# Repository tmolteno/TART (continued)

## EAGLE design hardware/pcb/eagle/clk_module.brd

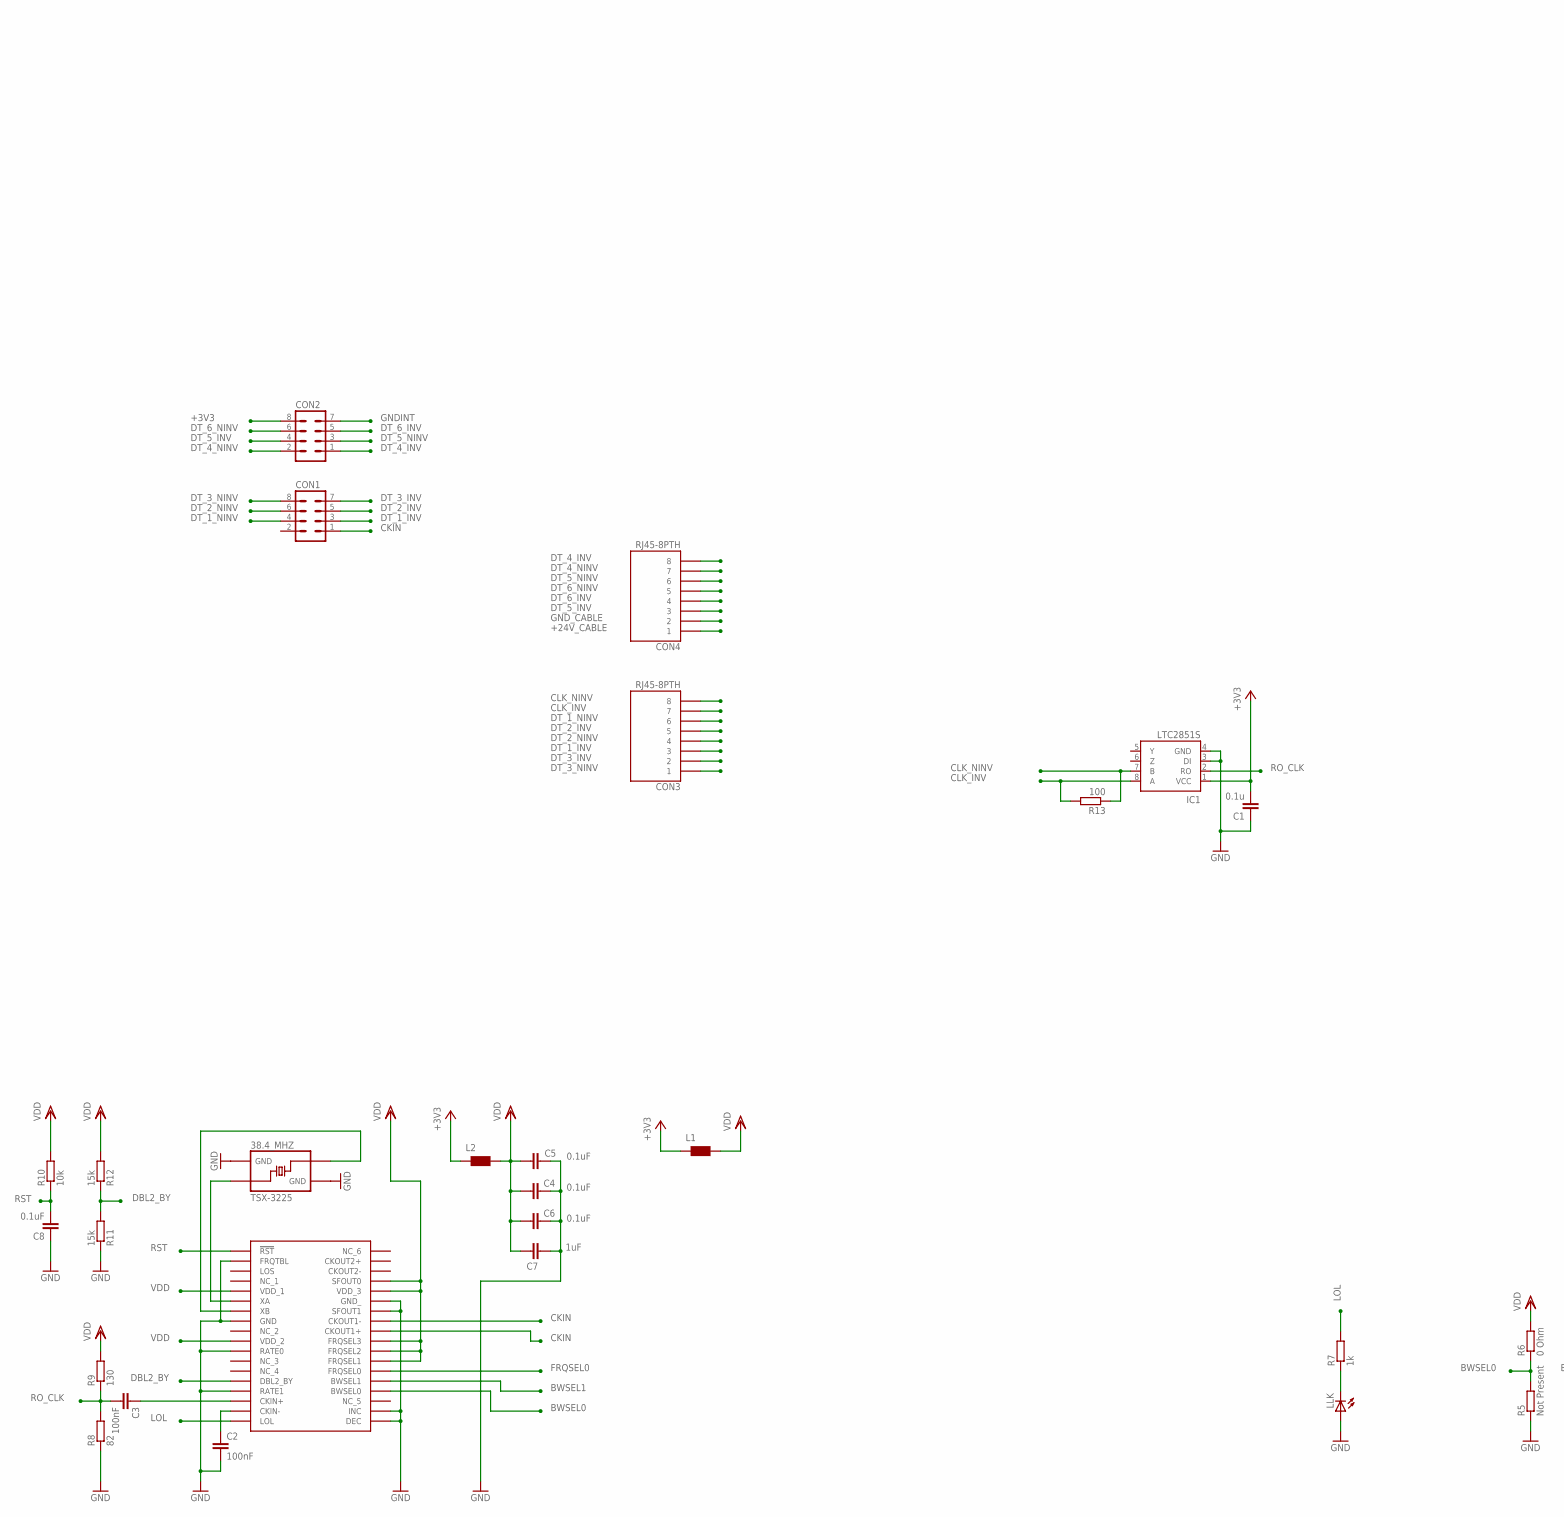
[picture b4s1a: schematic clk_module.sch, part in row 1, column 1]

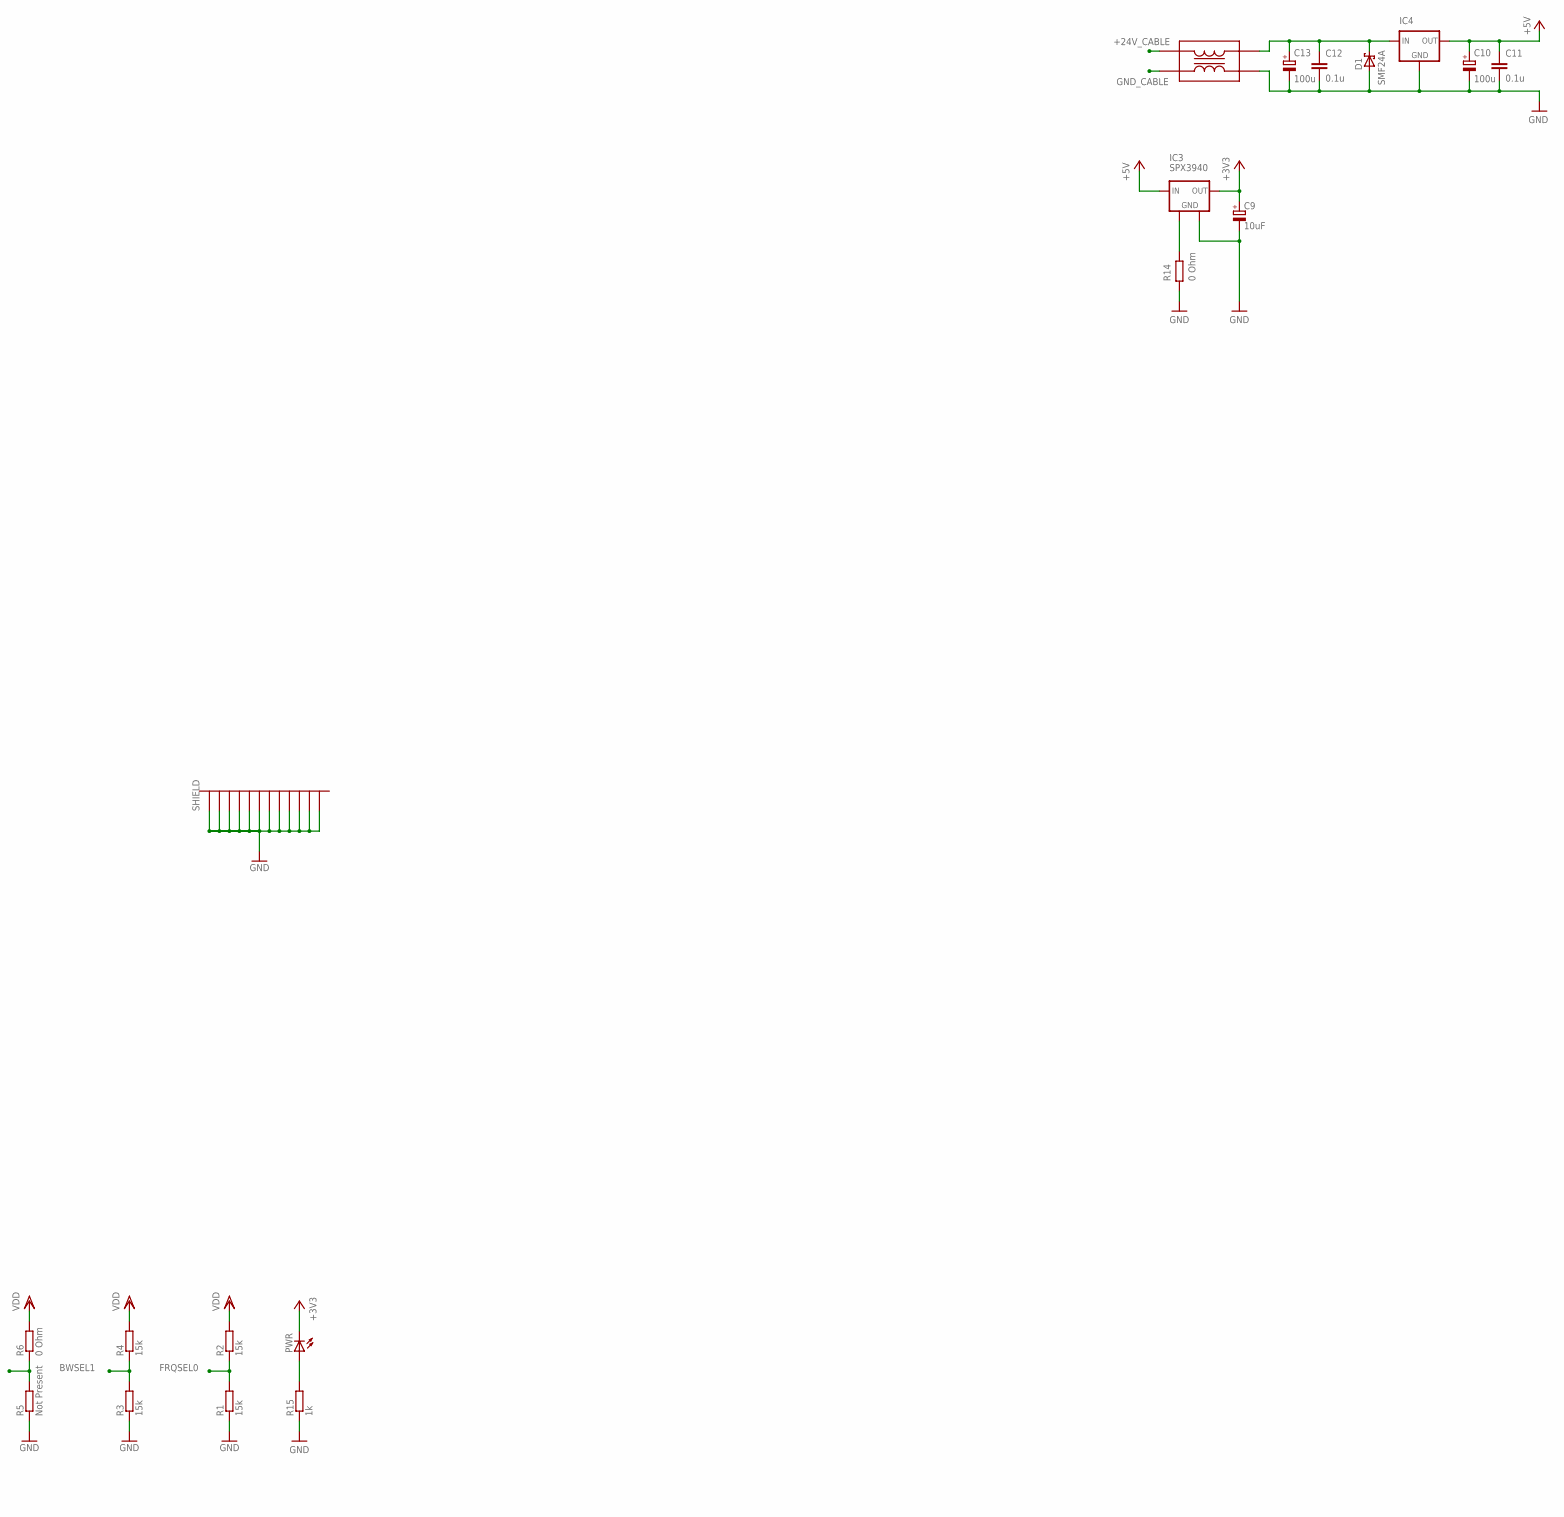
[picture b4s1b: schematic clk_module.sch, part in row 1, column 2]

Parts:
38.4_MHZ: TSX-3225
C1, C11, C12: 0.1u; C0805
C2, C3: 100nF; C0402
C4, C5, C6, C8: 0.1uF; C0402
C7: 1uF; C0402
C9: 10uF; E2-5
C10, C13: 100u; E5-10,5
CON1, CON2: MA04-2
CON3, CON4: RJ45-8PTH; RJ45-8
D1: SMF24A; SOD123
IC1: LTC2851S; SOIC8
IC2: SI5317; QFN-36
IC3: SPX3940; SOT223
IC4: V_REG_OKI-78SRSINK; TO220-IGO
L1, L2: WE-CBF_0805; 0805
L3: ACM3225-601-2P-T001
LLK: LEDCHIPLED_0805; CHIPLED_0805
PWR: LEDCHIPLED_0805; CHIPLED_0805
R1, R2, R3, R4, R11, R12: 15k; R0603
R5: Not Present; R0603
R6: 0 Ohm; R0603
R7, R15: 1k; R0603
R8: 82; R0603
R9: 130; R0603
R10: 10k; R0402
R13: 100; R0603
R14: 0 Ohm; R0805
SH1: BMIS-202

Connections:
24V_IN: C12.1, C13.+, D1.C, IC4.IN, L3.4
+3V3: C1.2, C9.+, CON2.8, IC1.1 (VCC), IC3.3 (OUT), L1.1, L2.1, PWR.C
+5V: C10.+, C11.1, IC3.1 (IN), IC4.OUT
+24V_CABLE: CON4.1, L3.1
BWSEL0: IC2.22 (BWSEL0), R5.2, R6.1
BWSEL1: IC2.23 (BWSEL1), R3.2, R4.1
CKIN: CON1.1, IC2.28 (CKOUT1+), IC2.29 (CKOUT1-)
CKIN+: C3.1, IC2.16 (CKIN+)
CKIN-: C2.1, IC2.17 (CKIN-)
CLK_INV: CON3.7, IC1.8 (A), R13.2
CLK_NINV: CON3.8, IC1.7 (B), R13.1
DBL2_BY: IC2.14 (DBL2_BY), R11.2, R12.1
DT_1_INV: CON1.3, CON3.3
DT_1_NINV: CON1.4, CON3.6
DT_2_INV: CON1.5, CON3.5
DT_2_NINV: CON1.6, CON3.4
DT_3_INV: CON1.7, CON3.2
DT_3_NINV: CON1.8, CON3.1
DT_4_INV: CON2.1, CON4.8
DT_4_NINV: CON2.2, CON4.7
DT_5_INV: CON2.4, CON4.3
DT_5_NINV: CON2.3, CON4.6
DT_6_INV: CON2.5, CON4.4
DT_6_NINV: CON2.6, CON4.5
FRQSEL0: IC2.24 (FRQSEL0), R1.2, R2.1
GND: 38.4_MHZ.PIN_2 (GND_2), 38.4_MHZ.PIN_4 (GND_1), C1.1, C2.2, C4.1, C5.1, C6.1, C7.1, C8.1, IC1.3 (DI), IC1.4 (GND), IC2.2 (FRQTBL), IC2.8 (GND), IC2.11 (RATE0), IC2.15 (RATE1), IC2.19 (DEC), IC2.20 (INC), IC2.30 (SFOUT1), IC2.31 (GND_), IC2.GND_PAD (GND), IC2.GND_VIA_1 (GND), IC2.GND_VIA_2 (GND), IC2.GND_VIA_3 (GND), IC2.GND_VIA_4 (GND), IC2.GND_VIA_5 (GND), LLK.A, R1.1, R3.1, R5.1, R8.1, R11.1, R14.1, SH1.P$1, SH1.P$2, SH1.P$3, SH1.P$4, SH1.P$5, SH1.P$6, SH1.P$7, SH1.P$8, SH1.P$9, SH1.P$10, SH1.P$11, SH1.P$12
GNDINT: C9.-, C10.-, C11.2, C12.2, C13.-, CON2.7, D1.A, IC3.2 (GND), IC3.4 (GND), IC4.GND, L3.3, R14.2, R15.1
GND_CABLE: CON4.2, L3.2
LOL: IC2.18 (LOL), R7.2
unnamed: PWR.A, R15.2
unnamed: LLK.C, R7.1
RO_CLK: C3.2, IC1.2 (RO), R8.2, R9.1
RST: C8.2, IC2.1 (!RST), R10.1
VDD: C4.2, C5.2, C6.2, C7.2, IC2.5 (VDD_1), IC2.10 (VDD_2), IC2.25 (FRQSEL1), IC2.26 (FRQSEL2), IC2.27 (FRQSEL3), IC2.32 (VDD_3), IC2.33 (SFOUT0), L2.2, R10.2, R12.2
VDD_2: L1.2, R2.2, R4.2, R6.2, R9.2
XA: 38.4_MHZ.PIN_1 (CON_1), IC2.6 (XA)
XB: 38.4_MHZ.PIN_3 (CON_2), IC2.7 (XB)

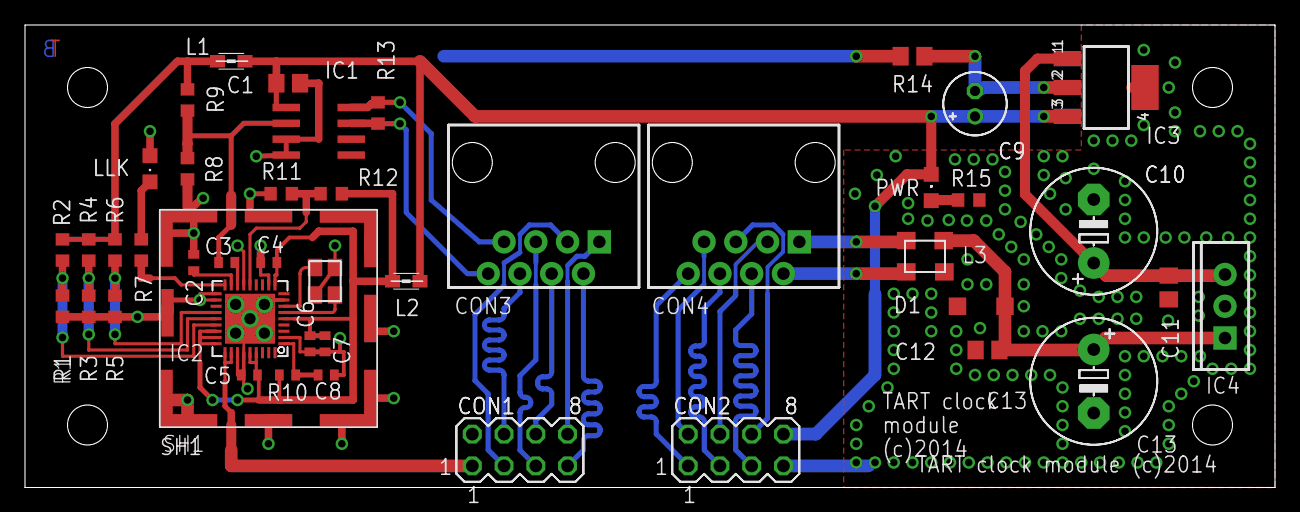
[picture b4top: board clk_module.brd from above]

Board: 2 copper layers, 100.0 x 37.0 mm, 44 parts (0 on the bottom side), 37 nets.

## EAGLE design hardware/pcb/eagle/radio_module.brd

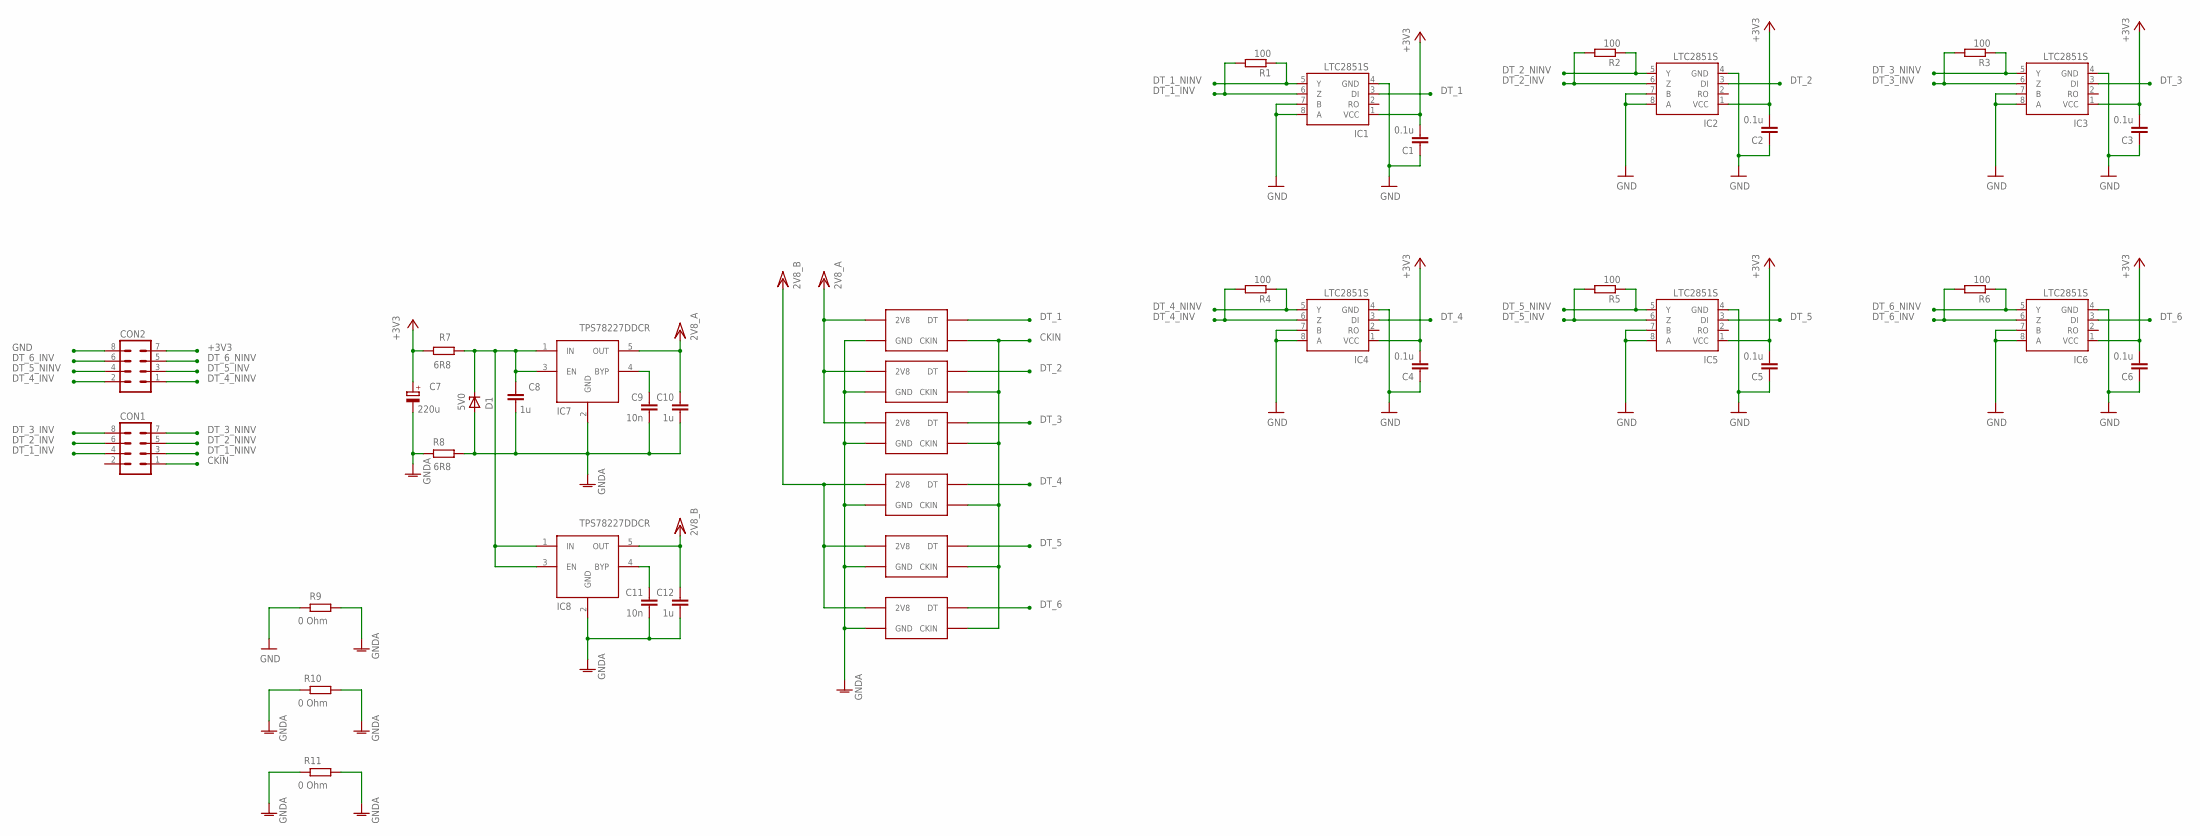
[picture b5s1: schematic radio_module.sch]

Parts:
C1, C2, C3, C4, C5, C6: 0.1u; C0805
C7: 220u; C1210
C8, C10, C12: 1u; C0603
C9, C11: 10n; C0603
CON1, CON2: MA04-2
D1: 5V0; SOD523
IC1, IC2, IC3, IC4, IC5, IC6: LTC2851S; SOIC8
IC7, IC8: TPS78227DDCR; SOT23-5
MOD_1, MOD_2, MOD_3, MOD_4, MOD_5, MOD_6: GPS_RADIO_MODULE
R1, R2, R3, R4, R5, R6: 100; R0603
R7: 6R8; R0805
R8: 6R8; R0603
R9, R10, R11: 0 Ohm; R0805

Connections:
+2V8_A: C10.1, IC7.5 (OUT), MOD_1.2V8@11 (2V8), MOD_1.2V8@15 (2V8), MOD_1.2V8@16 (2V8), MOD_2.2V8@11 (2V8), MOD_2.2V8@15 (2V8), MOD_2.2V8@16 (2V8), MOD_3.2V8@11 (2V8), MOD_3.2V8@15 (2V8), MOD_3.2V8@16 (2V8)
+2V8_B: C12.1, IC8.5 (OUT), MOD_4.2V8@11 (2V8), MOD_4.2V8@15 (2V8), MOD_4.2V8@16 (2V8), MOD_5.2V8@11 (2V8), MOD_5.2V8@15 (2V8), MOD_5.2V8@16 (2V8), MOD_6.2V8@11 (2V8), MOD_6.2V8@15 (2V8), MOD_6.2V8@16 (2V8)
+3V3: C1.2, C2.2, C3.2, C4.2, C5.2, C6.2, C7.1 (+), CON2.7, IC1.1 (VCC), IC2.1 (VCC), IC3.1 (VCC), IC4.1 (VCC), IC5.1 (VCC), IC6.1 (VCC), R7.2
BYP: C9.1, IC7.4 (BYP)
BYP1: C11.1, IC8.4 (BYP)
CKIN: CON1.1, MOD_1.CKIN@13 (CKIN), MOD_2.CKIN@13 (CKIN), MOD_3.CKIN@13 (CKIN), MOD_4.CKIN@13 (CKIN), MOD_5.CKIN@13 (CKIN), MOD_6.CKIN@13 (CKIN)
DT_1: IC1.3 (DI), MOD_1.DT@12 (DT)
DT_1_INV: CON1.4, IC1.6 (Z), R1.2
DT_1_NINV: CON1.3, IC1.5 (Y), R1.1
DT_2: IC2.3 (DI), MOD_2.DT@12 (DT)
DT_2_INV: CON1.6, IC2.6 (Z), R2.2
DT_2_NINV: CON1.5, IC2.5 (Y), R2.1
DT_3: IC3.3 (DI), MOD_3.DT@12 (DT)
DT_3_INV: CON1.8, IC3.6 (Z), R3.2
DT_3_NINV: CON1.7, IC3.5 (Y), R3.1
DT_4: IC4.3 (DI), MOD_6.DT@12 (DT)
DT_4_INV: CON2.2, IC4.6 (Z), R4.2
DT_4_NINV: CON2.1, IC4.5 (Y), R4.1
DT_5: IC5.3 (DI), MOD_5.DT@12 (DT)
DT_5_INV: CON2.3, IC5.6 (Z), R5.2
DT_5_NINV: CON2.4, IC5.5 (Y), R5.1
DT_6: IC6.3 (DI), MOD_4.DT@12 (DT)
DT_6_INV: CON2.6, IC6.6 (Z), R6.2
DT_6_NINV: CON2.5, IC6.5 (Y), R6.1
GND: C1.1, C2.1, C3.1, C4.1, C5.1, C6.1, CON2.8, IC1.4 (GND), IC1.7 (B), IC1.8 (A), IC2.4 (GND), IC2.7 (B), IC2.8 (A), IC3.4 (GND), IC3.7 (B), IC3.8 (A), IC4.4 (GND), IC4.7 (B), IC4.8 (A), IC5.4 (GND), IC5.7 (B), IC5.8 (A), IC6.4 (GND), IC6.7 (B), IC6.8 (A), R9.2
GNDA: C7.2 (-), C8.2, C9.2, C10.2, C11.2, C12.2, D1.A, IC7.2 (GND), IC8.2 (GND), MOD_1.GND@1 (GND), MOD_1.GND@2 (GND), MOD_1.GND@3 (GND), MOD_1.GND@4 (GND), MOD_1.GND@5 (GND), MOD_1.GND@6 (GND), MOD_1.GND@7 (GND), MOD_1.GND@8 (GND), MOD_1.GND@9 (GND), MOD_1.GND@10 (GND), MOD_1.GND@14 (GND), MOD_1.V1 (GND), MOD_1.V2 (GND), MOD_1.V3 (GND), MOD_1.V4 (GND), MOD_1.V5 (GND), MOD_1.V6 (GND), MOD_1.V7 (GND), MOD_1.V8 (GND), MOD_1.V9 (GND), MOD_1.V10 (GND), MOD_1.V11 (GND), MOD_1.V12 (GND), MOD_1.V13 (GND), MOD_1.V14 (GND), MOD_1.V15 (GND), MOD_1.V16 (GND), MOD_1.V17 (GND), MOD_1.V18 (GND), MOD_1.V19 (GND), MOD_1.V20 (GND), MOD_1.V21 (GND), MOD_1.V22 (GND), MOD_1.V23 (GND), MOD_1.V24 (GND), MOD_1.V25 (GND), MOD_1.V26 (GND), MOD_1.V27 (GND), MOD_1.V28 (GND), MOD_1.V29 (GND), MOD_1.V30 (GND), MOD_2.GND@1 (GND), MOD_2.GND@2 (GND), MOD_2.GND@3 (GND), MOD_2.GND@4 (GND), MOD_2.GND@5 (GND), MOD_2.GND@6 (GND), MOD_2.GND@7 (GND), MOD_2.GND@8 (GND), MOD_2.GND@9 (GND), MOD_2.GND@10 (GND), MOD_2.GND@14 (GND), MOD_2.V1 (GND), MOD_2.V2 (GND), MOD_2.V3 (GND), MOD_2.V4 (GND), MOD_2.V5 (GND), MOD_2.V6 (GND), MOD_2.V7 (GND), MOD_2.V8 (GND), MOD_2.V9 (GND), MOD_2.V10 (GND), MOD_2.V11 (GND), MOD_2.V12 (GND), MOD_2.V13 (GND), MOD_2.V14 (GND), MOD_2.V15 (GND), MOD_2.V16 (GND), MOD_2.V17 (GND), MOD_2.V18 (GND), MOD_2.V19 (GND), MOD_2.V20 (GND), MOD_2.V21 (GND), MOD_2.V22 (GND), MOD_2.V23 (GND), MOD_2.V24 (GND), MOD_2.V25 (GND), MOD_2.V26 (GND), MOD_2.V27 (GND), MOD_2.V28 (GND), MOD_2.V29 (GND), MOD_2.V30 (GND), MOD_3.GND@1 (GND), MOD_3.GND@2 (GND), MOD_3.GND@3 (GND), MOD_3.GND@4 (GND), MOD_3.GND@5 (GND), MOD_3.GND@6 (GND), MOD_3.GND@7 (GND), MOD_3.GND@8 (GND), MOD_3.GND@9 (GND), MOD_3.GND@10 (GND), MOD_3.GND@14 (GND), MOD_3.V1 (GND), MOD_3.V2 (GND), MOD_3.V3 (GND), MOD_3.V4 (GND), MOD_3.V5 (GND), MOD_3.V6 (GND), MOD_3.V7 (GND), MOD_3.V8 (GND), MOD_3.V9 (GND), MOD_3.V10 (GND)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
unnamed: C8.1, D1.C, IC7.1 (IN), IC7.3 (EN), IC8.1 (IN), IC8.3 (EN), R7.1

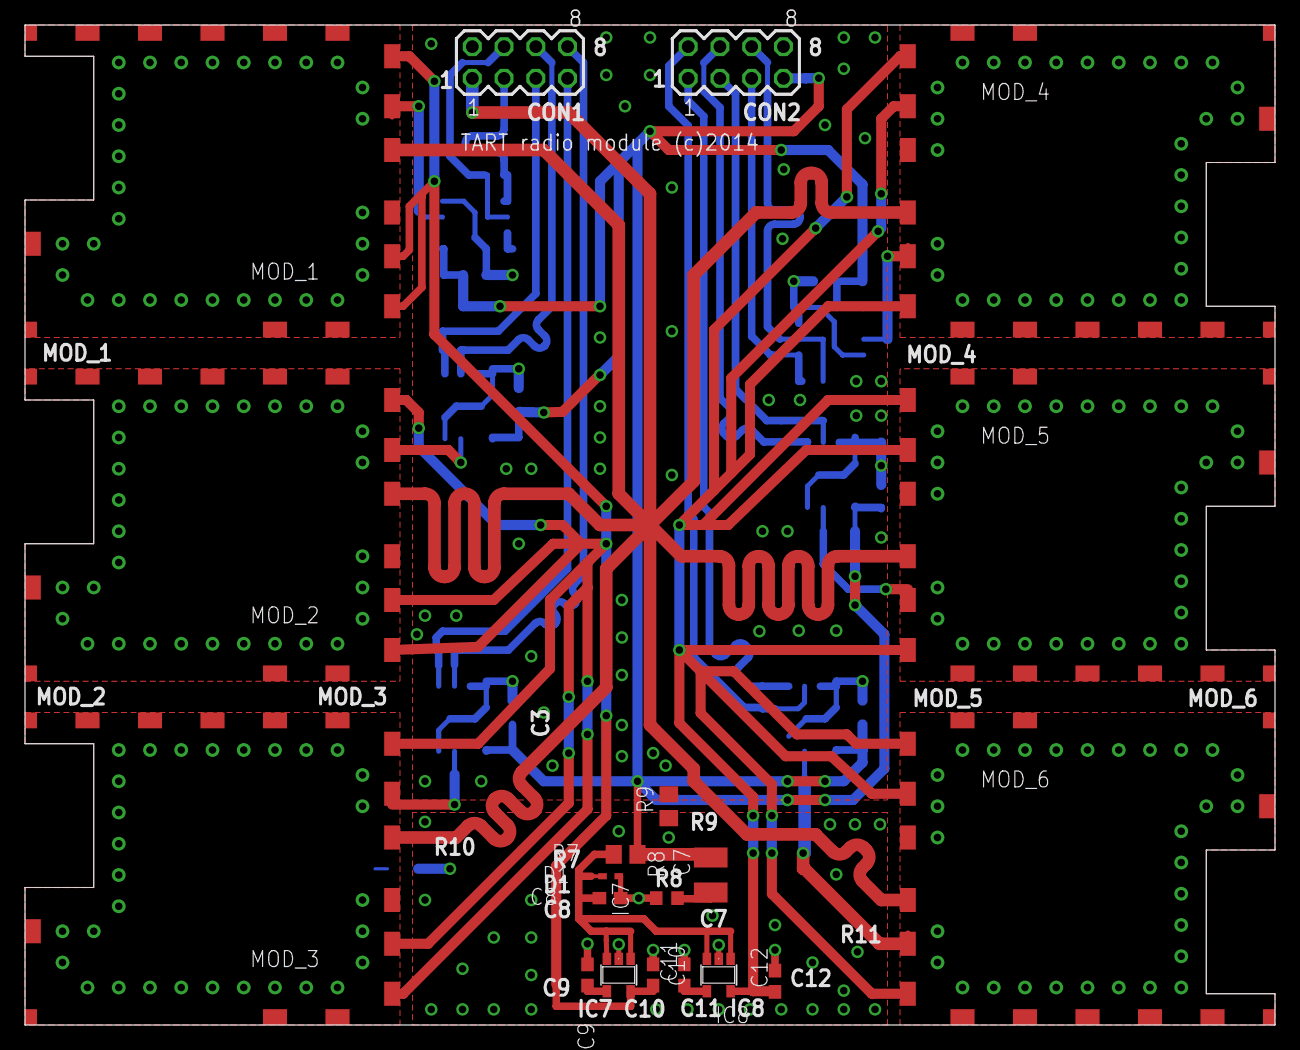
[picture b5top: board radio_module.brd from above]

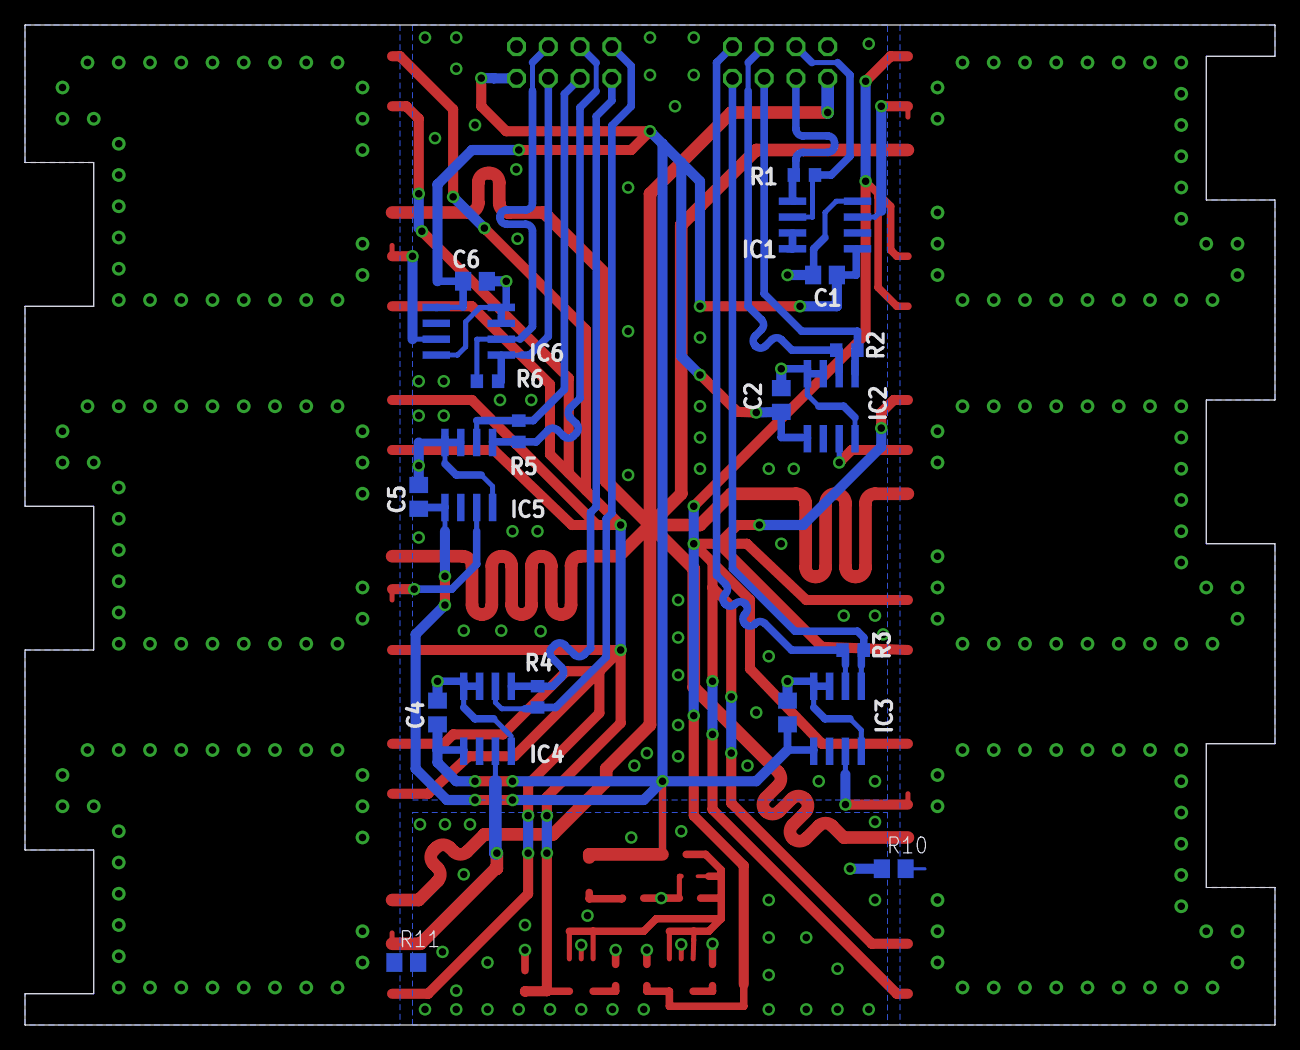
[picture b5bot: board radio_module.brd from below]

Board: 2 copper layers, 100.0 x 80.0 mm, 40 parts (20 on the bottom side), 27 nets.

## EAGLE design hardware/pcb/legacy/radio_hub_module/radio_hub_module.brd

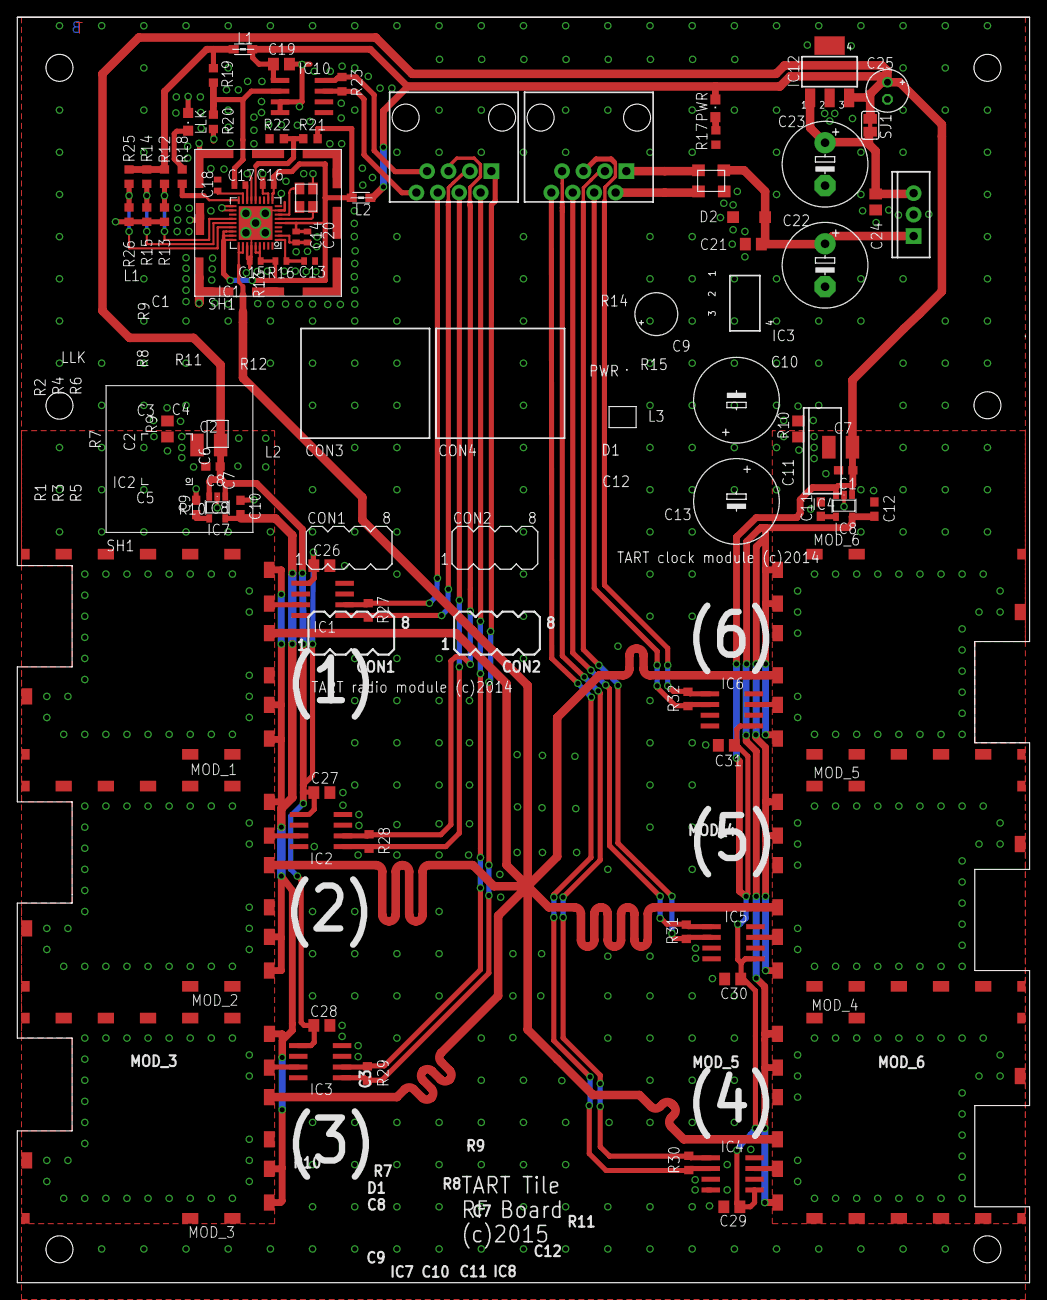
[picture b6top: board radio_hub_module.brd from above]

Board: 4 copper layers, 120.0 x 150.0 mm, 78 parts (0 on the bottom side), 48 nets.

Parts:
38.4_MHZ: TSX-3225
C1, C8, C10, C12: 1u; C0603
C2, C7: 220u; C1210
C9, C11: 10n; C0603
C13, C14, C15, C16: 0.1uF; C0402
C17, C18: 100nF; C0402
C19, C21, C24, C26, C27, C28, C29, C30, C31: 0.1u; C0805
C20: 1uF; C0402
C22, C23: 100u; E5-10,5
C25: 10uF; E2-5
CON3, CON4: RJ45-8PTH; RJ45-8
D2: SMF24A; SOD123
IC1, IC2, IC3, IC4, IC5, IC6, IC10: LTC2851S; SOIC8
IC7, IC8: TPS78227DDCR; SOT23-5
IC9: SI5317; QFN-36
IC11: OKI78s05; TO220-IGO
IC12: SPX3940; SOT223
L1, L2: 220w; 0805
L3: ACM3225-601-2P-T001
LLK: Grn; CHIPLED_0805
MOD_1, MOD_2, MOD_3, MOD_4, MOD_5, MOD_6: GPS_RADIO_MODULE
PWR: Red; CHIPLED_0805
R9, R10: 0 Ohm; R0805
R12: 0 Ohm; R0603
R13: Not Present; R0603
R14, R15, R21, R22, R25, R26: 15k; R0603
R16: 10k; R0402
R17, R18: 1k; R0603
R19: 130; R0603
R20: 82; R0603
R23, R27, R28, R29, R30, R31, R32: 100; R0603
SH1: BMIS-202
SJ1: SJ

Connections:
24V_IN: C21.1, C22.+, D2.C, IC11.IN, L3.4
!DT1: CON3.6, IC1.6, R27.2
!DT2: CON3.5, IC2.6, R28.2
!DT3: CON3.2, IC3.6, R29.2
!DT4: CON4.8, IC4.6, R30.2
!DT5: CON4.3, IC5.6, R31.2
!DT6: CON4.4, IC6.6, R32.2
!RST: C13.2, IC9.1, R16.1
+2V8_A: C10.1, IC7.5, MOD_1.2V8@11, MOD_1.2V8@15, MOD_1.2V8@16, MOD_2.2V8@11, MOD_2.2V8@15, MOD_2.2V8@16, MOD_3.2V8@11, MOD_3.2V8@15, MOD_3.2V8@16
+2V8_B: C12.1, IC8.5, MOD_4.2V8@11, MOD_4.2V8@15, MOD_4.2V8@16, MOD_5.2V8@11, MOD_5.2V8@15, MOD_5.2V8@16, MOD_6.2V8@11, MOD_6.2V8@15, MOD_6.2V8@16
+3V3: C1.1, C2.1, C7.1, C8.1, C19.2, C25.+, C26.2, C27.2, C28.2, C29.2, C30.2, C31.2, IC1.1, IC2.1, IC3.1, IC4.1, IC5.1, IC6.1, IC7.1, IC7.3, IC8.1, IC8.3, IC10.1, IC12.3, L1.1, L2.1, PWR.C, SJ1.2
+5V: C23.+, C24.1, IC11.OUT, IC12.1, SJ1.1
+24V_CABLE: CON4.1, L3.1
AGND: C2.2, C8.2, C9.2, C10.2, IC7.2, MOD_1.GND@1, MOD_1.GND@2, MOD_1.GND@3, MOD_1.GND@4, MOD_1.GND@5, MOD_1.GND@6, MOD_1.GND@7, MOD_1.GND@8, MOD_1.GND@9, MOD_1.GND@10, MOD_1.GND@14, MOD_1.V1, MOD_1.V2, MOD_1.V3, MOD_1.V4, MOD_1.V5, MOD_1.V6, MOD_1.V7, MOD_1.V8, MOD_1.V9, MOD_1.V10, MOD_1.V11, MOD_1.V12, MOD_1.V13, MOD_1.V14, MOD_1.V15, MOD_1.V16, MOD_1.V17, MOD_1.V18, MOD_1.V19, MOD_1.V20, MOD_1.V21, MOD_1.V22, MOD_1.V23, MOD_1.V24, MOD_1.V25, MOD_1.V26, MOD_1.V27, MOD_1.V28, MOD_1.V29, MOD_1.V30, MOD_2.GND@1, MOD_2.GND@2, MOD_2.GND@3, MOD_2.GND@4, MOD_2.GND@5, MOD_2.GND@6, MOD_2.GND@7, MOD_2.GND@8, MOD_2.GND@9, MOD_2.GND@10, MOD_2.GND@14, MOD_2.V1, MOD_2.V2, MOD_2.V3, MOD_2.V4, MOD_2.V5, MOD_2.V6, MOD_2.V7, MOD_2.V8, MOD_2.V9, MOD_2.V10, MOD_2.V11, MOD_2.V12, MOD_2.V13, MOD_2.V14, MOD_2.V15, MOD_2.V16, MOD_2.V17, MOD_2.V18, MOD_2.V19, MOD_2.V20, MOD_2.V21, MOD_2.V22, MOD_2.V23, MOD_2.V24, MOD_2.V25, MOD_2.V26, MOD_2.V27, MOD_2.V28, MOD_2.V29, MOD_2.V30, MOD_3.GND@1, MOD_3.GND@2, MOD_3.GND@3, MOD_3.GND@4, MOD_3.GND@5, MOD_3.GND@6, MOD_3.GND@7, MOD_3.GND@8, MOD_3.GND@9, MOD_3.GND@10, MOD_3.GND@14, MOD_3.V1, MOD_3.V2, MOD_3.V3, MOD_3.V4, MOD_3.V5, MOD_3.V6, MOD_3.V7, MOD_3.V8, MOD_3.V9, MOD_3.V10, MOD_3.V11, MOD_3.V12, MOD_3.V13, MOD_3.V14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
BWSEL0: IC9.22, R12.1, R13.2
BWSEL1: IC9.23, R14.1, R15.2
BYP: C9.1, IC7.4
BYP1: C11.1, IC8.4
CKIN: IC9.28, IC9.29, MOD_1.CKIN@13, MOD_2.CKIN@13, MOD_3.CKIN@13, MOD_4.CKIN@13, MOD_5.CKIN@13, MOD_6.CKIN@13
CKIN+: C17.1, IC9.16
CKIN-: C18.1, IC9.17
CLK_INV: CON3.7, IC10.8, R23.2
CLK_NINV: CON3.8, IC10.7, R23.1
DBL2_BY: IC9.14, R21.1, R22.2
DT1: CON3.3, IC1.5, R27.1
DT2: CON3.4, IC2.5, R28.1
DT3: CON3.1, IC3.5, R29.1
DT4: CON4.7, IC4.5, R30.1
DT5: CON4.6, IC5.5, R31.1
DT6: CON4.5, IC6.5, R32.1
DT_1: IC1.3, MOD_1.DT@12
DT_2: IC2.3, MOD_2.DT@12
DT_3: IC3.3, MOD_3.DT@12
DT_4: IC4.3, MOD_4.DT@12
DT_5: IC5.3, MOD_5.DT@12
DT_6: IC6.3, MOD_6.DT@12
FRQSEL0: IC9.24, R25.1, R26.2
GND: 38.4_MHZ.PIN_2, 38.4_MHZ.PIN_4, C13.1, C14.1, C15.1, C16.1, C18.2, C19.1, C20.1, C21.2, C22.-, C23.-, C24.2, C25.-, C26.1, C27.1, C28.1, C29.1, C30.1, C31.1, D2.A, IC1.4, IC1.7, IC1.8, IC2.4, IC2.7, IC2.8, IC3.4, IC3.7, IC3.8, IC4.4, IC4.7, IC4.8, IC5.4, IC5.7, IC5.8, IC6.4, IC6.7, IC6.8, IC9.2, IC9.8, IC9.11, IC9.15, IC9.19, IC9.20, IC9.30, IC9.31, IC9.GND_PAD, IC9.GND_VIA_1, IC9.GND_VIA_2, IC9.GND_VIA_3, IC9.GND_VIA_4, IC9.GND_VIA_5, IC10.3, IC10.4, IC11.GND, IC12.2, IC12.4, L3.3, LLK.A, R9.2, R10.2, R13.1, R15.1, R17.1, R20.1, R22.1, R26.1, SH1.P$1, SH1.P$2, SH1.P$3, SH1.P$4, SH1.P$5, SH1.P$6, SH1.P$7, SH1.P$8, SH1.P$9, SH1.P$10, SH1.P$11, SH1.P$12
GNDA: C1.2, C7.2, C11.2, C12.2, IC8.2, MOD_4.GND@1, MOD_4.GND@2, MOD_4.GND@3, MOD_4.GND@4, MOD_4.GND@5, MOD_4.GND@6, MOD_4.GND@7, MOD_4.GND@8, MOD_4.GND@9, MOD_4.GND@10, MOD_4.GND@14, MOD_4.V1, MOD_4.V2, MOD_4.V3, MOD_4.V4, MOD_4.V5, MOD_4.V6, MOD_4.V7, MOD_4.V8, MOD_4.V9, MOD_4.V10, MOD_4.V11, MOD_4.V12, MOD_4.V13, MOD_4.V14, MOD_4.V15, MOD_4.V16, MOD_4.V17, MOD_4.V18, MOD_4.V19, MOD_4.V20, MOD_4.V21, MOD_4.V22, MOD_4.V23, MOD_4.V24, MOD_4.V25, MOD_4.V26, MOD_4.V27, MOD_4.V28, MOD_4.V29, MOD_4.V30, MOD_5.GND@1, MOD_5.GND@2, MOD_5.GND@3, MOD_5.GND@4, MOD_5.GND@5, MOD_5.GND@6, MOD_5.GND@7, MOD_5.GND@8, MOD_5.GND@9, MOD_5.GND@10, MOD_5.GND@14, MOD_5.V1, MOD_5.V2, MOD_5.V3, MOD_5.V4, MOD_5.V5, MOD_5.V6, MOD_5.V7, MOD_5.V8, MOD_5.V9, MOD_5.V10, MOD_5.V11, MOD_5.V12, MOD_5.V13, MOD_5.V14, MOD_5.V15, MOD_5.V16, MOD_5.V17, MOD_5.V18, MOD_5.V19, MOD_5.V20, MOD_5.V21, MOD_5.V22, MOD_5.V23, MOD_5.V24, MOD_5.V25, MOD_5.V26, MOD_5.V27, MOD_5.V28, MOD_5.V29, MOD_5.V30, MOD_6.GND@1, MOD_6.GND@2, MOD_6.GND@3, MOD_6.GND@4, MOD_6.GND@5, MOD_6.GND@6, MOD_6.GND@7, MOD_6.GND@8, MOD_6.GND@9, MOD_6.GND@10, MOD_6.GND@14, MOD_6.V1, MOD_6.V2, MOD_6.V3, MOD_6.V4, MOD_6.V5, MOD_6.V6, MOD_6.V7, MOD_6.V8, MOD_6.V9, MOD_6.V10, MOD_6.V11, MOD_6.V12, MOD_6.V13, MOD_6.V14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
GND_CABLE: CON4.2, L3.2
LOL: IC9.18, R18.2
unnamed: PWR.A, R17.2
unnamed: LLK.C, R18.1
RO_CLK: C17.2, IC10.2, R19.1, R20.2
VDD: C14.2, C15.2, C16.2, C20.2, IC9.5, IC9.10, IC9.25, IC9.26, IC9.27, IC9.32, IC9.33, L2.2, R16.2, R21.2
VDD_2: L1.2, R12.2, R14.2, R19.2, R25.2
XA: 38.4_MHZ.PIN_1, IC9.6
XB: 38.4_MHZ.PIN_3, IC9.7

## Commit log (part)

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2018-09-16 Added a little more context to the descri the description of the calibration
2018-09-20 Version bump and streamline dockerfiles
2018-09-20 Ignore node_modules in the docker files
2018-09-20 Use docker-compose to deploy the object position server
2018-09-28 Updated calibration docs.
2018-09-28 More doc cleanup, fix links
2018-09-28 Add a couple of containers for debug app builds - they reload when code is changed
2018-10-15 Added two QZS satellites to the correct list
2019-02-03 Some documentation cleanup
2019-02-06 Slight documentation improvements
2019-02-10 Improved install instructions with links.
2019-02-11 Added links to API documentation
2019-02-14 Add converted kicad projects
2019-02-14 Modify to upload antenna positions (take into account the rotation reported by the calibration)
2019-02-15 Updated the api handler to throw errors, and report SUCCESS when appropriate. Bump version and update dependencies. Closes #32 and Issue #38
2019-02-21 Move all the update and packages into a single command. This follows best practices and avoids stale apt caches
2019-02-21 Move to buster and python3
2019-02-21 Further python3 compatibility
2019-02-21 Added BOM stuff
2019-02-22 Change config attribute for num_antenna to get_num_antenna()
2019-02-22 Getting tests slowly working
2019-02-23 Updated API usage
2019-02-26 Import time, and catch exception correctly
2019-02-26 Moved things around so that old files are in the legacy directory
2019-02-27 Moved to directly using markdown from within setuptools
2019-03-03 Added a tunelling comment
2019-03-04 Some lint cleanup
2019-03-06 Finally working
2019-03-06 Now going
2019-03-06 Added argument parsing. Bringing up to date
2019-03-07 Added manifests
2019-03-08 Next step is visibility files
2019-03-09 Added HDF5 export and import for visibility objects
2019-03-10 Added dockerised testbench
2019-03-11 Update to add correct docker dependencies
2019-03-12 Clean up old compiled python files being used in the docker. HDF file saving now working
2019-03-12 Move to python3, handle HDF files
2019-03-12 Updated observation load to choose HDF files if the extension is right. Refers to Issue #40
2019-03-13 Update testbench to add visibility exporters for HDF format, and to rename Visibility_Load/Save to list_load and list_save, since they do not actually save individual visibility objects. Related to I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
2019-03-14 Better command line parsing, and check that the user specifies at least one option of data to download
2019-03-14 New raw data download function in tart tools
2019-03-14 Very slight typo in logging code
2019-05-08 Added a put method
2019-05-15 Update install instructions
2019-06-18 Updated README to reflect some pre-requisites. Relates to Issue #41
2019-07-02 Visibilities now stored as HDF5 files. Closes Issue #40
2019-07-08 Add some test dependencies
2019-07-24 Update to use new HDF data and python3 changes
2019-07-25 Added the raw image
2019-10-02 Added a timeout to HTTP requests
2019-11-05 Change table name to parameter
2019-11-06 Minor doc improvements
2019-11-06 Update to get locales right for casa
2019-11-06 Have added UVW data. fits file seems blank
2019-11-06 Have added many many tables
2019-11-07 Allow getting of information for the measurement set from the RESTful API
2020-02-20 Added docker-compose file for the VPN upstream connection
2020-03-15 Bump acorn from 5.1.2 to 5.7.4 in /software/containers/web_app/web-app
    Bumps [acorn](https://github.com/acornjs/acorn) from 5.1.2 to 5.7.4.
    - [Release notes](https://github.com/acornjs/acorn/releases)
    - [Commits](https://github.com/acornjs/acorn/compare/5.1.2...5.7.4)
2020-06-25 Bump rack in /software/containers/ephemeris_server/code
    Bumps [rack](https://github.com/rack/rack) from 1.6.11 to 2.1.4.
    - [Release notes](https://github.com/rack/rack/releases)
    - [Changelog](https://github.com/rack/rack/blob/master/CHANGELOG.md)
    - [Commits](https://github.com/rack/rack/compare/1.6.11...2.1.4)
2020-08-09 Add a header, and remove a special character in a comment
2020-08-25 Add gains and phases to stored hdf files
2020-09-14 Tag release 2.1. Closes #43
2021-03-08 Bump elliptic in /software/containers/web_app/web-app
    Bumps [elliptic](https://github.com/indutny/elliptic) from 6.5.0 to 6.5.4.
    - [Release notes](https://github.com/indutny/elliptic/releases)
    - [Commits](https://github.com/indutny/elliptic/compare/v6.5.0...v6.5.4)
2021-03-11 Fix jwt import
2021-04-12 Return a dict from the visibility.from_hdf5() method
2021-04-12 Minor documentation tweak
2021-04-14 Better baselines as lists
2021-05-07 Bump lodash in /software/containers/web_app/web-app
    Bumps [lodash](https://github.com/lodash/lodash) from 4.17.11 to 4.17.21.
    - [Release notes](https://github.com/lodash/lodash/releases)
    - [Commits](https://github.com/lodash/lodash/compare/4.17.11...4.17.21)
2021-05-19 Reformat code. Fix bug in get-gains handling in tart_calibrate
2021-05-19 Clean code using black
2021-05-27 Bump dns-packet in /software/containers/web_app/web-app
    Bumps [dns-packet](https://github.com/mafintosh/dns-packet) from 1.3.1 to 1.3.4.
    - [Release notes](https://github.com/mafintosh/dns-packet/releases)
    - [Changelog](https://github.com/mafintosh/dns-packet/blob/master/CHANGELOG.md)
    - [Commits](https://github.com/mafintosh/dns-packet/compare/v1.3.1...v1.3.4)
2021-06-11 Add resdme
2021-06-15 Removed hostname
2021-08-06 Reformat and port to python3
2021-10-05 Bump url-parse in /software/containers/web_app/web-app
    Bumps [url-parse](https://github.com/unshiftio/url-parse) from 1.4.7 to 1.5.3.
    - [Release notes](https://github.com/unshiftio/url-parse/releases)
    - [Commits](https://github.com/unshiftio/url-parse/compare/1.4.7...1.5.3)
    ---
    updated-dependencies:
    - dependency-name: url-parse
2021-11-04 Added template for gridless_wasm
2021-11-08 Cleaner code to do conditional assignment
2021-11-08 Added headers
2021-11-08 Library now returns a string
2021-11-11 example without bundler
2021-11-11 added wasm build dir for tart-vuer
2021-11-24 Added a README for build instructions
2021-12-04 Fix bug where spaces in satellite names causes a crash.
2021-12-14 Leave elevation and azimuth in degrees. Update max nside to 64
2022-01-09 Update docker-compose-telescope.yml
    Can directly run "docker-compose -f docker-compose-telescope.yml up --build"
2022-01-09 Update README.md
    Guide update
2022-01-21 Create fp-info-cache
2022-02-11 Bump karma from 4.1.0 to 6.3.14 in /software/containers/web_app/web-app
    Bumps [karma](https://github.com/karma-runner/karma) from 4.1.0 to 6.3.14.
    - [Release notes](https://github.com/karma-runner/karma/releases)
    - [Changelog](https://github.com/karma-runner/karma/blob/master/CHANGELOG.md)
    - [Commits](https://github.com/karma-runner/karma/compare/v4.1.0...v6.3.14)
    ---
    updated-dependencies:
2022-02-23 Compose for Rhodes
2022-02-26 Bump url-parse in /software/containers/web_app/web-app
    Bumps [url-parse](https://github.com/unshiftio/url-parse) from 1.4.7 to 1.5.10.
    - [Release notes](https://github.com/unshiftio/url-parse/releases)
    - [Commits](https://github.com/unshiftio/url-parse/compare/1.4.7...1.5.10)
    ---
    updated-dependencies:
    - dependency-name: url-parse
2022-04-01 Use k8 to run the script
2022-04-12 Bump nokogiri in /software/containers/ephemeris_server/code
    Bumps [nokogiri](https://github.com/sparklemotion/nokogiri) from 1.10.4 to 1.13.4.
    - [Release notes](https://github.com/sparklemotion/nokogiri/releases)
    - [Changelog](https://github.com/sparklemotion/nokogiri/blob/v1.13.4/CHANGELOG.md)
    - [Commits](https://github.com/sparklemotion/nokogiri/compare/v1.10.4...v1.13.4)
    ---
    updated-dependencies:
2022-05-02 support more flexible visibilities of baselines. selector for antennas in frontend. selector for tart api endpoint in frontend
2022-05-07 added deployment docs. fixed typo. staged build for rust->wasm and fronten.
2022-05-16 accept update
2022-06-01 Bump eventsource in /software/containers/web_app/web-app
    Bumps [eventsource](https://github.com/EventSource/eventsource) from 1.0.7 to 1.1.1.
    - [Release notes](https://github.com/EventSource/eventsource/releases)
    - [Changelog](https://github.com/EventSource/eventsource/blob/master/HISTORY.md)
    - [Commits](https://github.com/EventSource/eventsource/compare/v1.0.7...v1.1.1)
    ---
    updated-dependencies:
2022-06-20 Add ElAz test harness
2022-06-20 Update to modern development style. Add options to do a better fit
2022-06-20 Update scripts
2022-06-21 Added a --n parameter to stop after this many downloads
2022-06-21 Update with better help
2022-06-23 Update to use GHCR
2022-06-30 Remove duplicate classes that are in the tart codebase
2022-07-05 Remove objects that are now being used from tart.util
2022-07-05 Bump follow-redirects in /software/containers/web_app/web-app
    Bumps [follow-redirects](https://github.com/follow-redirects/follow-redirects) from 1.7.0 to 1.15.1.
    - [Release notes](https://github.com/follow-redirects/follow-redirects/releases)
    - [Commits](https://github.com/follow-redirects/follow-redirects/compare/v1.7.0...v1.15.1)
    ---
    updated-dependencies:
    - dependency-name: follow-redirects
2022-07-06 Moved to new repo
2022-07-23 Added north arm orientation and three arm survey
2022-07-25 Some data is here
2022-07-27 Added more measurements
2022-08-03 Add trigger ls command
2022-09-26 Bump degenerator and snyk in /software/containers/web_app/web-app
    Removes [degenerator](https://github.com/TooTallNate/node-degenerator). It's no longer used after updating ancestor dependency [snyk](https://github.com/snyk/snyk). These dependencies need to be upda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
    Removes `degenerator`
    Updates `snyk` from 1.134.2 to 1.1012.0
    - [Release notes](https://github.com/snyk/snyk/releases)
    - [Commits](https://github.com/snyk/snyk/compare/v1.134.2...v1.1012.0)
    ---
2022-10-21 Bump nokogiri in /software/containers/ephemeris_server/code
    Bumps [nokogiri](https://github.com/sparklemotion/nokogiri) from 1.13.6 to 1.13.9.
    - [Release notes](https://github.com/sparklemotion/nokogiri/releases)
    - [Changelog](https://github.com/sparklemotion/nokogiri/blob/main/CHANGELOG.md)
    - [Commits](https://github.com/sparklemotion/nokogiri/compare/v1.13.6...v1.13.9)
    ---
    updated-dependencies:
2022-11-15 Update Dockerfiles
2022-12-02 Bump decode-uri-component in /software/containers/web_app/web-app
    Bumps [decode-uri-component](https://github.com/SamVerschueren/decode-uri-component) from 0.2.0 to 0.2.2.
    - [Release notes](https://github.com/SamVerschueren/decode-uri-component/releases)
    - [Commits](https://github.com/SamVerschueren/decode-uri-component/compare/v0.2.0...v0.2.2)
    ---
    updated-dependencies:
    - dependency-name: decode-uri-component
2022-12-21 Add an elevation attribute for much smaller downloads
2023-02-01 Update rust packages
2023-10-13 Added five arm survey
2023-10-18 Update for Rhodes. Fix error in calculating bearing angle
2023-11-10 Added old antenna positions
2023-11-18 Use the new celestrak API
2025-03-27 Clean up code and update
